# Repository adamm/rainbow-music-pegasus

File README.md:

# Rainbow Music Pegasus

Disclaimer: This work is a *work-in-progress*.  This project is still under
active development and is estimated to be completed _Spring 2027_.
What you see here is code that is largely incomplete, buggy, probably crashes,
and could catch fire. The PCB board is largely inefficient, expensive,
probably broken, and could catch fire.

## Description

Rainbow Music Pegasus is a combination 3D printed horse coupled with a PCB
with 10 or more RGB lights, microphone, and a MCU.  A
[Fast Fourier transform](https://en.wikipedia.org/wiki/Fast_Fourier_transform)
algorithm translates an audio signal from the microphone, which is displayed
as a flashing colour light display as the horse's wings.

The original design from the horse is from Stlflix, but its internals were
not adequate to support the PCB.  As a result I completely remapped all
vertices, and designed the internal mount to hold the PCB unit vertically.

## Design

The PCB features an ESP32-C3 MCU, a PUI Audio AOM-5024P-HD-MB-R electret
microphone, an OPA2322 dual amplifier with an MCP41050 digital potentiometer,
up to 24 WS2812B RGB LEDs, and an MCP73831 battery charging circuit.  The full schematic is in
[schematic.pdf](schematic.pdf) and the parts list is in [bom.csv](bom.csv).

[View on KiCanvas](https://kicanvas.org/?github=https%3A%2F%2Fgithub.com%2Fadamm%2Frainbow-music-pegasus%2Fblob%2Fmaster%2Fpcb%2Frainbow-music-pegasus.kicad_pro)

## History

Version 1.0 of the rainbow-music-pegasus was completed March 2024.  A few
test units were sold at Breyer West show, but were never mass produced.
This version lacks wifi, bluetooth, and battery support.

Version 1.1 added a battery and charging module, battery status lights, and adjusting the position of the LEDs.

Version 1.2 is under active development. It will clean up the amp's stage-1
and digipot controlled stage-2, make use of the set-mode button, use USB-C
to charge, and other bug fixes. It is estimated to be completed Spring
2027.

## Battery

Use a single-cell (3.7V nominal) LiPo of 400mAh or larger, connected to the
JST PH connector J3.  The MCP73831 charges at a fixed 200mA (set by R10 and
R11), which keeps the charge rate at or below 0.5C for a 400mAh cell.  Larger
batteries are fine but take longer to charge: roughly 4 hours for 800mAh and
10 hours for 2000mAh.

When the battery runs low (under about 3.6V), the first light in each wing
blinks red every 3 seconds.  The rest of the light show carries on as usual.
The blinking stops once the battery is charging:

- **v1.1**: once charging brings the battery back over 3.7V.
- **v1.2**: within 10 seconds of plugging in USB.  While USB is plugged in,
  v1.2 measures the USB supply rather than the battery.

## Repository layout

| Path                 | Contents |
|----------------------|----------|
| [firmware/](firmware/) | ESP-IDF firmware for the ESP32-C3 (see its [README](firmware/README.md)) |
| [pcb/](pcb/)           | KiCad project, 3D models and gerbers |
| [stl/](stl/)           | Pegasus model (Blender, STL, 3MF), PCB model and SMT stencil mount (OpenSCAD) |
| [assets/](assets/)     | Images used in this README |
| [schematic.pdf](schematic.pdf) | Exported schematic |
| [bom.csv](bom.csv)     | Bill of materials |

Clone with submodules to get the Espressif KiCad libraries:

```sh
git clone --recurse-submodules https://github.com/adamm/rainbow-music-pegasus.git
```

## Building the firmware

The firmware uses ESP-IDF v5.x:

```sh
cd firmware
idf.py set-target esp32c3
idf.py build
idf.py -p <PORT> flash monitor
```

See [firmware/README.md](firmware/README.md) for the pin map, the LED-count
jumpers and how the audio pipeline works.

## Mic sensitivity

The microphone's sensitivity adjusts automatically.  If the sound is too
quiet it is turned up, and if it is so loud the wings stay at full
brightness it is turned down.  For 3 seconds after power-on, the wings will
appear to "flap" in white while the sensitivity settles to the room.  When
the device is moved between quiet and loud environments, it takes a few
seconds to catch up.

## Noisy rooms

The wings can show music over the sound of a crowd talking.  The pegasus keeps
learning each room's background sound, and lights up only for sound well
above it, such as the music's beats.  It follows a crowd as it gets louder
or quieter over several seconds.  Anything that holds steady, like a long
note, is learned too and fades away after about 20 seconds.  The music has
to be louder than the crowd, at least on its beats, to show.

## Set Mode

v1.1 has a new "Set Mode" button.  The intention is to flip between LED
animation modes, and to do a factory reset.

*Important*: Development of the button has not yet started but planned to be
ready Spring 2027 as v1.2.

## TODO

- [X] Release v1 for Breyer West 2024
- [X] Listen to music
- [X] Interpret music signal into the light show
- [X] Support a rechargable LiPo battery
- [X] Low battery warning
- [X] Replace USB-mini with USB-C for power
- [ ] Support a longer external LED string at 5V power and signal
- [ ] Implement "Set Mode" button
- [ ] Release v1.2 for Calgary Makerfaire 2027
- [ ] Sync with nearby horses for an enhanced light show
- [ ] Control of colour modes and settings via Web Bluetooth
- [ ] Firmware updates over BLE

## AI Use Disclaimer

This project was 100% derrived and created by me, with the following
assistance/exceptions that were created by Claude:

- [Schematic] Optimization of the analogue audio resistors and capacitors
- [Firmware] Dynamic volume adjustment based upon audio input thresholds
- [Firmware] Writing unit tests and a test harness
- [Firmware] Optimization of the FFT algorithm for the ESP32-C3
- [Firmware] Creating a process to filter out background audio in noisy rooms
- [Documentation] Creating general and firmware READMEs

## License

See [LICENSE.md](LICENSE.md) (Apache 2.0).

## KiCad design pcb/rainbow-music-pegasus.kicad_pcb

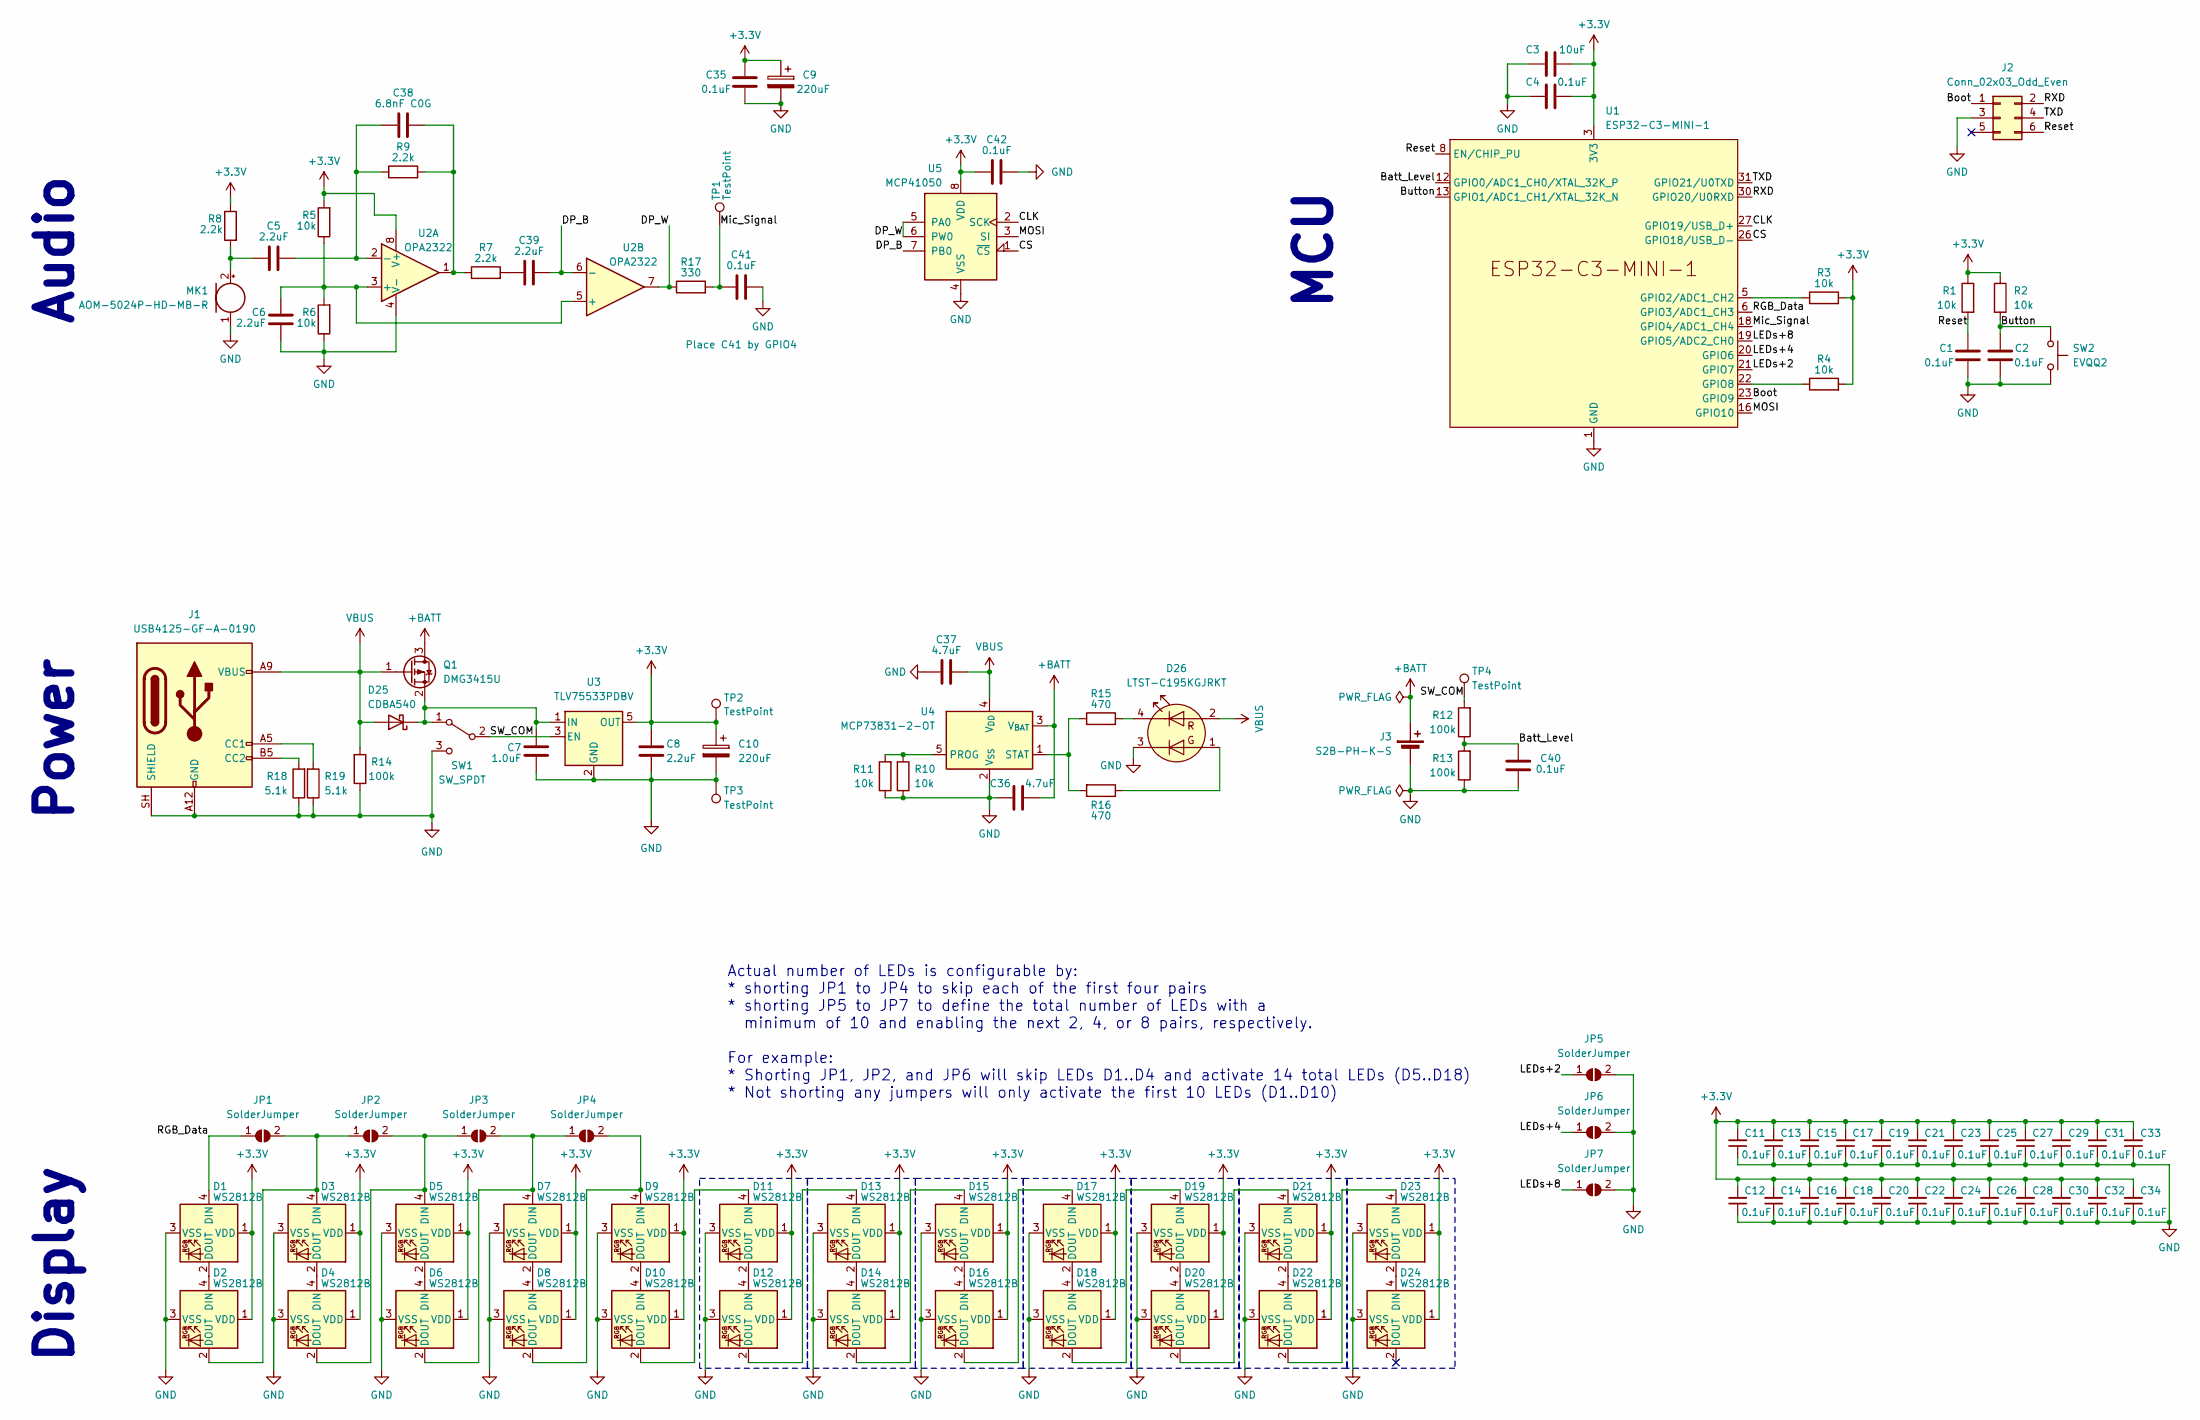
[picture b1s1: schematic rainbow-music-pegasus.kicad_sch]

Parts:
C1, C2, C4: 0.1uF; C_0805_2012Metric
C3: 10uF; C_0805_2012Metric
C5, C6, C8, C39: 2.2uF; C_0805_2012Metric
C7: 1.0uF; C_0805_2012Metric
C9, C10: 220uF; CP_Elec_5x5.9
C11, C12, C13, C14, C15, C16, C17, C18, C19, C20, C21, C22, C23, C24, C25, C26, C27, C28, C29, C30, C31, C32, C33, C34, C35, C40, C41, C42: 0.1uF; C_0603_1608Metric
C36, C37: 4.7uF; C_0805_2012Metric
C38: 6.8nF C0G; C_0805_2012Metric
D1, D2, D3, D4, D5, D6, D7, D8, D9, D10, D11, D12, D13, D14, D15, D16, D17, D18, D19, D20, D21, D22, D23, D24: WS2812B; LED_WS2812B_PLCC4_5.0x5.0mm_P3.2mm
D25: CDBA540; D_SMA
D26: LTST-C195KGJRKT
J1: USB4125-GF-A-0190; USB_C_Receptacle_GCT_USB4125-xx-x-0190_6P_TopMnt_Horizontal
J2: Conn_02x03_Odd_Even; PinHeader_2x03_P2.54mm_Vertical
J3: S2B-PH-K-S; JST_PH_S2B-PH-K_1x02_P2.00mm_Horizontal
JP1, JP2, JP3, JP4, JP5, JP6, JP7: SolderJumper; SolderJumper-2_P1.3mm_Open_TrianglePad1.0x1.5mm
MK1: AOM-5024P-HD-MB-R; PinHeader_1x02_P2.54mm_Vertical
Q1: DMG3415U; SOT-23
R1, R2, R3, R4, R5, R6, R10, R11: 10k; R_0805_2012Metric
R7, R8, R9: 2.2k; R_0805_2012Metric
R12, R13, R14: 100k; R_0805_2012Metric
R15, R16: 470; R_0603_1608Metric
R17: 330; R_0805_2012Metric
R18, R19: 5.1k; R_0603_1608Metric
SW1: SW_SPDT; SW_Slide_SPDT_Angled_CK_OS102011MA1Q
SW2: EVQQ2; SW_SPST_EVQQ2
TP1, TP2, TP3, TP4: TestPoint; TestPoint_THTPad_1.5x1.5mm_Drill0.7mm
U1: ESP32-C3-MINI-1
U2: OPA2322; SOIC-8_3.9x4.9mm_P1.27mm
U3: TLV75533PDBV; SOT-23-5
U4: MCP73831-2-OT; SOT-23-5
U5: MCP41050; SOIC-8_3.9x4.9mm_P1.27mm

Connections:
+3.3V: C3.2, C4.2, C8.2, C9.1, C10.1, C11.2, C12.2, C13.2, C14.2, C15.2, C16.2, C17.2, C18.2, C19.2, C20.2, C21.2, C22.2, C23.2, C24.2, C25.2, C26.2, C27.2, C28.2, C29.2, C30.2, C31.2, C32.2, C33.2, C34.2, C35.2, C42.1, D1.1 (VDD), D2.1 (VDD), D3.1 (VDD), D4.1 (VDD), D5.1 (VDD), D6.1 (VDD), D7.1 (VDD), D8.1 (VDD), D9.1 (VDD), D10.1 (VDD), D11.1 (VDD), D12.1 (VDD), D13.1 (VDD), D14.1 (VDD), D15.1 (VDD), D16.1 (VDD), D17.1 (VDD), D18.1 (VDD), D19.1 (VDD), D20.1 (VDD), D21.1 (VDD), D22.1 (VDD), D23.1 (VDD), D24.1 (VDD), R1.1, R2.1, R3.2, R4.2, R5.2, R8.1, TP2.1 (1_1), U1.3 (3V3), U2.8 (V+), U3.5 (OUT), U5.8 (VDD)
+BATT: C36.2, J3.1 (+), Q1.3 (D), U4.3 (V_{BAT})
/Batt_Level: C40.1, R12.1, R13.2, U1.12 (GPIO0/ADC1_CH0/XTAL_32K_P)
/Boot: J2.1, U1.23 (GPIO9)
/Button: C2.2, R2.2, SW2.1, U1.13 (GPIO1/ADC1_CH1/XTAL_32K_N)
/CLK: U1.27 (GPIO19/USB_D+), U5.2 (SCK)
/CS: U1.26 (GPIO18/USB_D-), U5.1 (~CS)
/DP_B: C39.2, U2.6 (-), U5.7 (PB0)
/DP_W: R17.1, U2.7, U5.5 (PA0), U5.6 (PW0)
/LEDs+2: JP5.1 (A), U1.21 (GPIO7)
/LEDs+4: JP6.1 (A), U1.20 (GPIO6)
/LEDs+8: JP7.1 (A), U1.19 (GPIO5/ADC2_CH0)
/MOSI: U1.16 (GPIO10), U5.3 (SI)
/Mic_Signal: C41.1, R17.2, TP1.1 (1_1), U1.18 (GPIO4/ADC1_CH4)
/RGB_Data: D1.4 (DIN), JP1.1 (A), U1.6 (GPIO3/ADC1_CH3)
/RXD: J2.2, U1.30 (GPIO20/U0RXD)
/Reset: C1.2, J2.6, R1.2, U1.8 (EN/CHIP_PU)
/SW_COM: R12.2, SW1.2 (B), TP4.1 (1_1), U3.3 (EN)
/TXD: J2.4, U1.31 (GPIO21/U0TXD)
GND: C1.1, C2.1, C3.1, C4.1, C6.1, C7.1, C8.1, C9.2, C10.2, C11.1, C12.1, C13.1, C14.1, C15.1, C16.1, C17.1, C18.1, C19.1, C20.1, C21.1, C22.1, C23.1, C24.1, C25.1, C26.1, C27.1, C28.1, C29.1, C30.1, C31.1, C32.1, C33.1, C34.1, C35.1, C36.1, C37.1, C40.2, C41.2, C42.2, D1.3 (VSS), D2.3 (VSS), D3.3 (VSS), D4.3 (VSS), D5.3 (VSS), D6.3 (VSS), D7.3 (VSS), D8.3 (VSS), D9.3 (VSS), D10.3 (VSS), D11.3 (VSS), D12.3 (VSS), D13.3 (VSS), D14.3 (VSS), D15.3 (VSS), D16.3 (VSS), D17.3 (VSS), D18.3 (VSS), D19.3 (VSS), D20.3 (VSS), D21.3 (VSS), D22.3 (VSS), D23.3 (VSS), D24.3 (VSS), D26.3 (K2), J1.A12 (GND), J1.B12 (GND), J1.SH (SHIELD), J2.3, J3.2 (-), JP5.2 (B), JP6.2 (B), JP7.2 (B), MK1.1 (-), R6.1, R10.1, R11.1, R13.1, R14.1, R18.1, R19.1, SW1.3 (C), SW2.2, TP3.1 (1_1), U1.1 (GND), U1.2 (GND), U1.11 (GND), U1.14 (GND), U1.36 (GND), U1.37 (GND), U1.38 (GND), U1.39 (GND), U1.40 (GND), U1.41 (GND), U1.42 (GND), U1.43 (GND), U1.44 (GND), U1.45 (GND), U1.46 (GND), U1.47 (GND), U1.48 (GND), U1.49 (GND), U1.50 (GND), U1.51 (GND), U1.52 (GND), U1.53 (GND), U2.4 (V-), U3.2 (GND), U4.2 (V_{SS}), U5.4 (VSS)
unnamed: C38.1, R7.1, R9.2, U2.1
unnamed: C39.1, R7.2
unnamed: D1.2 (DOUT), D2.4 (DIN)
unnamed: D2.2 (DOUT), D3.4 (DIN), JP1.2 (B), JP2.1 (A)
unnamed: D3.2 (DOUT), D4.4 (DIN)
unnamed: D4.2 (DOUT), D5.4 (DIN), JP2.2 (B), JP3.1 (A)
unnamed: D5.2 (DOUT), D6.4 (DIN)
unnamed: D6.2 (DOUT), D7.4 (DIN), JP3.2 (B), JP4.1 (A)
unnamed: D7.2 (DOUT), D8.4 (DIN)
unnamed: D8.2 (DOUT), D9.4 (DIN), JP4.2 (B)
unnamed: D9.2 (DOUT), D10.4 (DIN)
unnamed: D10.2 (DOUT), D11.4 (DIN)
unnamed: D11.2 (DOUT), D12.4 (DIN)
unnamed: D12.2 (DOUT), D13.4 (DIN)
unnamed: D13.2 (DOUT), D14.4 (DIN)
unnamed: D14.2 (DOUT), D15.4 (DIN)
unnamed: D15.2 (DOUT), D16.4 (DIN)
unnamed: D16.2 (DOUT), D17.4 (DIN)
unnamed: D17.2 (DOUT), D18.4 (DIN)
unnamed: D18.2 (DOUT), D19.4 (DIN)
unnamed: D19.2 (DOUT), D20.4 (DIN)
unnamed: D20.2 (DOUT), D21.4 (DIN)
unnamed: D21.2 (DOUT), D22.4 (DIN)
unnamed: D22.2 (DOUT), D23.4 (DIN)
unnamed: D23.2 (DOUT), D24.4 (DIN)
unnamed: C7.2, D25.1 (K), Q1.2 (S), SW1.1 (A), U3.1 (IN)
unnamed: D26.1 (A2), R16.1
unnamed: D26.4 (K1), R15.2
unnamed: J1.A5 (CC1), R19.2
unnamed: J1.B5 (CC2), R18.2
unnamed: C5.1, MK1.2 (+), R8.2
unnamed: R3.1, U1.5 (GPIO2/ADC1_CH2)
unnamed: R4.1, U1.22 (GPIO8)
unnamed: C6.2, R5.1, R6.2, U2.3 (+), U2.5 (+)
unnamed: C5.2, C38.2, R9.1, U2.2 (-)
unnamed: R10.2, R11.2, U4.5 (PROG)
unnamed: R15.1, R16.2, U4.1 (STAT)
VBUS: C37.2, D25.2 (A), D26.2 (A1), J1.A9 (VBUS), J1.B9 (VBUS), Q1.1 (G), R14.2, U4.4 (V_{DD})

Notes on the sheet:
Display
Actual number of LEDs is configurable by: * shorting JP1 to JP4 to skip each of the first four pairs * shorting JP5 to JP7 to define the total number of LEDs with a minimum of 10 and enabling the next 2, 4, or 8 pairs, respectively. For example: * Shorting JP1, JP2, and JP6 will skip LEDs D1..D4 an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
Audio
MCU
Power

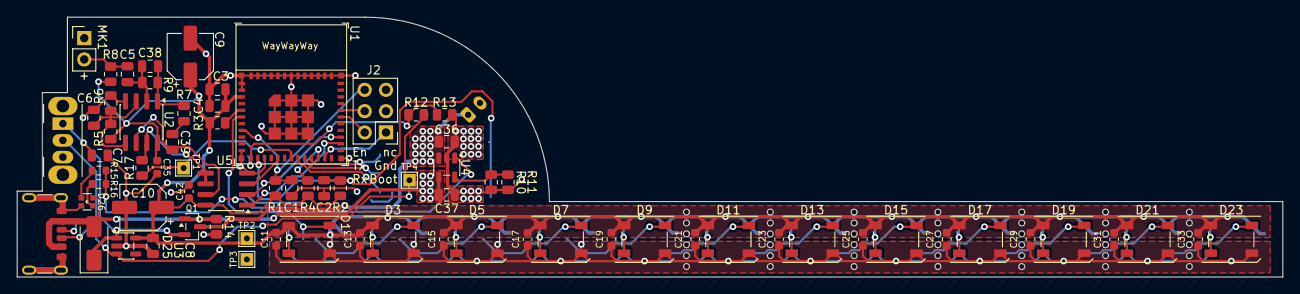
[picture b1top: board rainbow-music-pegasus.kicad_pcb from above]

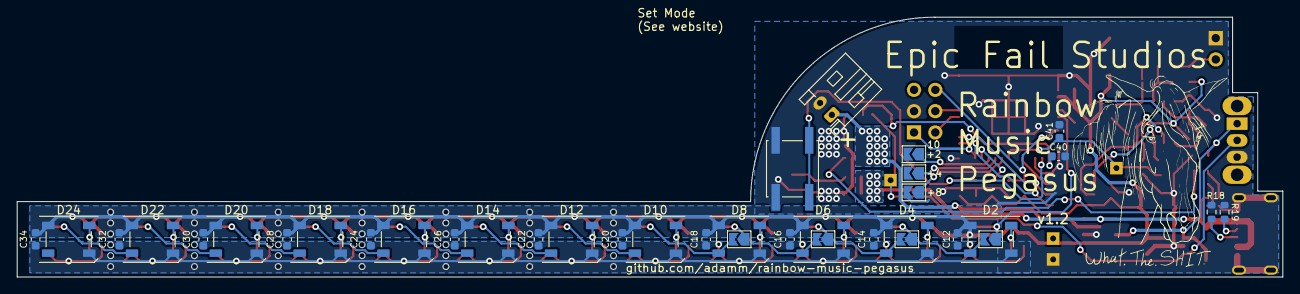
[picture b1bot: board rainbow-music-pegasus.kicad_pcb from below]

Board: 2 copper layers, 151.0 x 31.0 mm, 110 parts (37 on the bottom side), 58 nets.

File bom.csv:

"Reference","Value","Footprint","Description","Quantity"
"C1, C2, C4","0.1uF","Capacitor_SMD:C_0805_2012Metric","","3"
"C3","10uF","Capacitor_SMD:C_0805_2012Metric","","1"
"C5, C6, C8, C39","2.2uF","Capacitor_SMD:C_0805_2012Metric","","4"
"C7","1.0uF","Capacitor_SMD:C_0805_2012Metric","","1"
"C9, C10","220uF","Capacitor_SMD:CP_Elec_5x5.9","","2"
"C11-C35, C40-C42","0.1uF","Capacitor_SMD:C_0603_1608Metric","Place C41 by GPIO4","28"
"C36, C37","4.7uF","Capacitor_SMD:C_0805_2012Metric","","2"
"C38","6.8nF C0G","Capacitor_SMD:C_0805_2012Metric","","1"
"D1-D24","WS2812B","LED_SMD:LED_WS2812B_PLCC4_5.0x5.0mm_P3.2mm","","24"
"D25","CDBA540","Diode_SMD:D_SMA","","1"
"D26","LTST-C195KGJRKT","Altivo:LTST-C195KGJRKT","LED dual red/green, 4-pin","1"
"J1","USB4125-GF-A-0190","Altivo:USB_C_Receptacle_GCT_USB4125-xx-x-0190_6P_TopMnt_Horizontal","USB Power-Only 6P Type-C Receptacle connector","1"
"J3","S2B-PH-K-S","Connector_JST:JST_PH_S2B-PH-K_1x02_P2.00mm_Horizontal","","1"
"MK1","AOM-5024P-HD-MB-R","Connector_PinHeader_2.54mm:PinHeader_1x02_P2.54mm_Vertical","","1"
"Q1","DMG3415U","Package_TO_SOT_SMD:SOT-23","","1"
"R1-R6, R10, R11","10k","Resistor_SMD:R_0805_2012Metric","","8"
"R7-R9","2.2k","Resistor_SMD:R_0805_2012Metric","","3"
"R12-R14","100k","Resistor_SMD:R_0805_2012Metric","","3"
"R15, R16","470","Resistor_SMD:R_0603_1608Metric","","2"
"R17","330","Resistor_SMD:R_0805_2012Metric","","1"
"R18, R19","5.1k","Resistor_SMD:R_0603_1608Metric","","2"
"SW1","SW_SPDT","Button_Switch_THT:SW_Slide_SPDT_Angled_CK_OS102011MA1Q","","1"
"SW2","EVQQ2","Button_Switch_SMD:SW_SPST_EVQQ2","","1"
"U1","ESP32-C3-MINI-1","PCM_Espressif:ESP32-C3-MINI-1","","1"
"U2","OPA2322","Package_SO:SOIC-8_3.9x4.9mm_P1.27mm","","1"
"U3","TLV75533PDBV","Package_TO_SOT_SMD:SOT-23-5","","1"
"U4","MCP73831-2-OT","Package_TO_SOT_SMD:SOT-23-5","","1"
"U5","MCP41050","Package_SO:SOIC-8_3.9x4.9mm_P1.27mm","","1"

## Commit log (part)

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2023-08-19 Initial commit showing first build of super-simple light flasher to sound
    Only supports brightness-by-amplitute so far
2023-08-20 Actually flash ws2812 array with the music
2023-08-20 Attempt to add on a decay to avoid overly-strong strong light effect
2023-08-21 Fine tune output to be sparkly and more accurate to frequency responses
2023-08-22 Adjusted color distribution so red in base, green in mid, blue in treble
2023-09-10 Major rewrite to get a working FFT library
2023-09-10 Include blender build files of the design
2023-10-15 Double the size of the horse, increase the total neopixel LEDs to 21
2024-02-03 Preliminary rainbow-music-pegasus firmware
2024-02-03 Initial commit to PCB design
2024-02-04 Updated git submodules to external resources
2024-02-04 Begin schematic and PCB layout
2024-02-04 Removed esp32-wifi-manager due to dependency conflict with esp-dsp/mdns
2024-02-05 POC of ADC+FFT
    Currently using a third-party FFT via https://github.com/fakufaku/esp32-fft
    instead of the esp-dsp version provided by espressif.
2024-02-07 Working design of FFT and light show -- still requires calibration
    Ported ArduinoFFT to run under esp-idf
2024-02-07 Working PCB design using esp32c3 and 20 ws2812b LEDs -- BOM pending validation
2024-02-07 Deprecate Arduino version of rmp firmware
2024-02-10 Finalize PCB layout for first production run
2024-02-10 Added a few test points for power. Committing gerbers
2024-02-11 Added Altivo cartoon to silkscreen, jumpers for configuring total LEDs installed
2024-02-12 Firmware code to apply configuration set by JP5, JP6, JP7
2024-02-12 Missed a decoupling capacitor at U2; added as C35
2024-02-13 Allow for configurable sample rate (using JP5, JP6, JP7) and add sound calibration routine (to remove ambient noise from sound analysis)
2024-02-13 Added in a simple decay so the lights aren't so flickery
2024-02-14 Footprint verification done, ready for first production run!
2024-02-14 Snapshots of ths BOM, Schematics; added license and readme starter.
2024-02-17 Added a simple scanning effect on the lights while calibrating light show to background noise
2024-02-18 Snapshot the completed pegasus design w/ preliminary placement of the PCB within
2024-02-18 Adding renderings of the PCB and the final pegasus w/ lights
2024-02-19 Tune the placement of the PCB within the Pegasus.
2024-03-02 Created a solder stencil mount to hold the PCB level with components already installed on underside
2024-03-02 Clean up logic for the PCB which alternates LEDs left to right in series
    When assigning the FFT values to the RGB LEDs, the right side gets the
    green byte first. Left side gets the blue byte first. This results in
    a symmetrical brightness but asymmetrical colour when comparing
    right-side and left-side LEDs.
    "Thin" tones that span single FFT column will produce red, green, and blue.
    "Thick" tones that span multiple FFT column will produce yellow, cyan, magenta,
2024-03-24 Transition from UltiMarker Cura to PrusaSlicer; other various cleanups so the PCB fits in the pegasus design
    Cura couldn't handle some edges resulting in several mis-prints.
2024-03-24 Updated the 3d render snapshot, bom, and gerbers
2024-03-24 Finalized battery design including charging status lights
2024-03-24 Adjust colour timings to be better aligned
2024-03-24 Added Battery charging module and a new mode-setting button
    Also found 3d models for the microphone, switch, USB components
2024-03-24 Added PrusaSlicer project config
2024-03-24 Increase the size of Altivo's picture on the back silkscreen
2024-03-24 Updated the README with the project's status/history
2024-03-24 Updated schematics.pdf to v1.1 design, link to KiCanvas
2024-03-25 Update the PCB template to include the arc, new usb placement
2024-03-29 Round out the ground fill zone using an arc margin
    Looks much nicer than eyeballing the fill zone into an arc-like shape by
    point
2024-04-01 Minor updates from feedback
    * Move the WayWayWay to be underneith U1, replaced "Antenna Area"
    * Added solderpaste to thru-holes on J1, makes the Micro-USB jack more secure
2024-04-08 Add on a digital potentiometer and a dual-channel amp to dynamically capture quiet or loud music
    Includes major realignment of entire top-left corner, chip changes,
    rerouting traces, etc.
2024-05-11 Updated gerbers, schematics, BOM to match recent pcb layout updates
2026-03-26 Update design to KiCad 9
2026-03-26 Refresh gerbers
2026-03-26 Update readme with goal to be ready for Calgary Makerfaire
2026-03-27 Minor corrections for the pcb stl negative, and
    * Corrected the rounded edge to be ⌀44mm
    * Removed the indent for the mic from v1.0
    * Corrected the height to 31mm
2026-04-05 Rename adc.c, adc.h to mic.c, mic.h
    Since we'll be using another ADC GPIO for battery level testing,
    renaming adc.[ch] to mic.[ch] makes sense.
2026-04-05 Stub in digipot SPI interface for controling input volume level
2026-04-05 Bump to esp-idf 5.5.1
2026-04-05 Cleaned up the stencil mount for first production run
2026-04-05 Init/Deinit Digipot MCP41050 via SPI
2026-04-09 Move TP6 to the DP_Wiper, add TP7 to DP_A and TP8 to MIC feed
    Also fixed the size of all Touchpoints to allow for soldering thru-hole pins
2026-05-31 Normalize the LED brightness during initialization routine
2026-05-31 Correct the tag for the microphone logs
2026-05-31 Implement the set_value() function for the MCP41050
2026-05-31 Claude had some useful suggestions to fix some bugs I didn't even know existed.
    - main.c: Fixed sampling delay — vTaskDelay(pdMS_TO_TICKS(sampling_period_us / 1000))
    performed integer division yielding zero, so samples were taken as
    fast as the MCU could run instead of at 10 kHz. Replaced with
    esp_rom_delay_us(sampling_period_us).
    - mic.c: Fixed crash when ADC calibration is unavailable — mic_read()
    unconditionally passed mic_cali_channel_handle to
2026-05-31 Simplify the leds_scanning() to use a stack array, not a heap allocation.
    This was another Claude suggestion that I wanted to clarify.
    #TIL you must cast {0} to have it apply as a compound literal. Neat!
2026-05-31 Upgrade to KiCAD 10
    Also resized Altivo to better fit in available back silkscreen area
